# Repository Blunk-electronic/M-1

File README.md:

# SYSTEM M-1
## An OpenSource Boundary Scan Test System (JTAG / IEEE1149.x) for:
- design checking
- low level hardware testing and repairing
- detection of opens, shorts, misloaded parts
- bring-up of prototypes and systems
- system testing in the field

### Test Pattern Generators and UUT data structures open for:
- interaction with In-Circuit and Flying Probe Test
- interaction optical inspection (AOI/AXI)
- customer specific requirements and extensions

### Special Features
- highly scripting capable
- files ASCII based and well suitable for version control with git
- programming language to write test programs
- runs natively on Linux
- source code written in Ada (for mission critical applications)
- rugged boundary scan controller hardware for industrial and educational purposes

### Boundary Scan Controller OpenSource:

- the boundary scan controller for training, development and education:

### Why Ada ??
- The only programming language that provides a robust and strong typing system is Ada.
- Objects and structures within such a test system are very complex things and require sound modelling.
- If saftey/mission critical and military applications use Ada, then is must be good for such a system as well.
- Ada is defined by ISO/IEC 8652:2012 and MIL-STD-1815
- Ada is beautiful :-)

### More Download Stuff
- find training material and user manual at http://www.blunk-electronic.de/products.html

### Collaboration
- We need a nice web site for the project.
- You are highly welcome !

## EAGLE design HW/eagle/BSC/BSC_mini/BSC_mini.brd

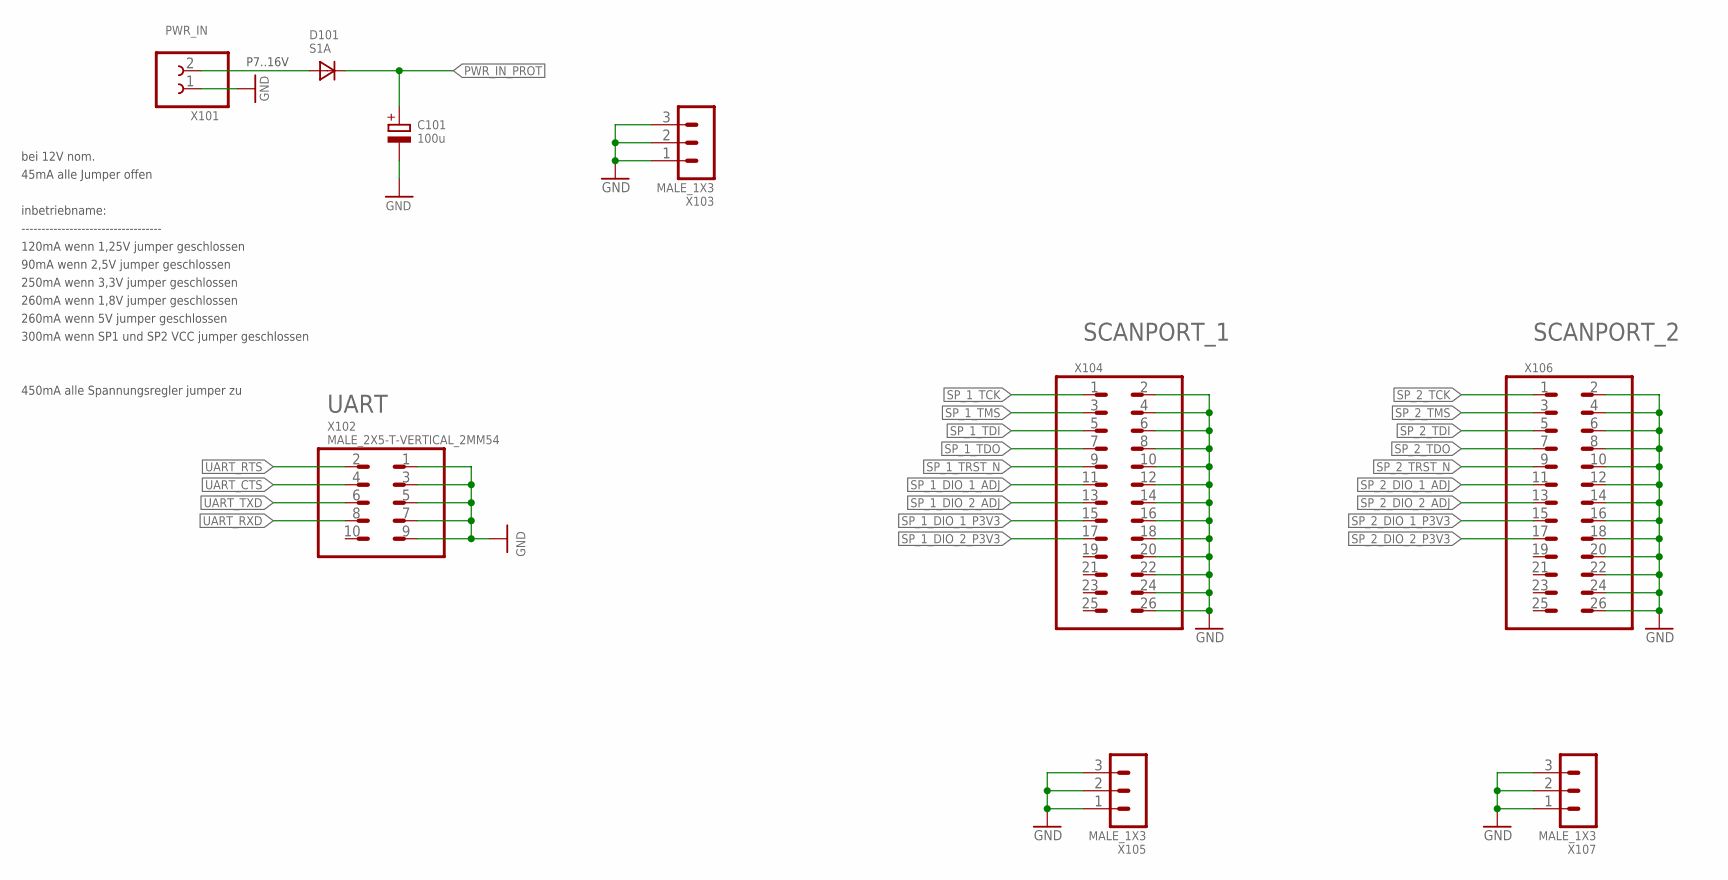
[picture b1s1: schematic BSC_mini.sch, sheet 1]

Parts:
C101: 100u; S_RADIAL_10MM; PART_CODE_BEL C_PAC_S_RADIAL_10mm_VAL_100u_Vmax_50V
D101: S1A; S_DO214AC; PART_CODE_BEL D_PAC_S_DO214AC_VAL_S1A
X101: CLAMP_1X2-T-2.5MM; T_WIRE_CLAMP_1X2_PITCH_2MM5
X102: MALE_2X5-T-VERTICAL_2MM54; T_MALE_2X5_VERTICAL_PITCH_2MM54
X103, X105, X107: MALE_1X3; T_MALE_3X1_VERTICAL
X104, X106: MALE_2X13-T-VERTICAL_PITCH_2MM54; T_MALE_2X13_VERTICAL_PITCH_2MM54

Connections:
GND: C101.-, X101.1, X102.1, X102.3, X102.5, X102.7, X102.9, X103.1, X103.2, X103.3, X104.2, X104.4, X104.6, X104.8, X104.10, X104.12, X104.14, X104.16, X104.18, X104.20, X104.22, X104.24, X104.26, X105.1, X105.2, X105.3, X106.2, X106.4, X106.6, X106.8, X106.10, X106.12, X106.14, X106.16, X106.18, X106.20, X106.22, X106.24, X106.26, X107.1, X107.2, X107.3; also elsewhere on the board
PWR_IN: D101.A, X101.2
PWR_IN_PROT: C101.+, D101.C; also elsewhere on the board
SP_1_DIO_1_ADJ: X104.11; also elsewhere on the board
SP_1_DIO_1_P3V3: X104.15; also elsewhere on the board
SP_1_DIO_2_ADJ: X104.13; also elsewhere on the board
SP_1_DIO_2_P3V3: X104.17; also elsewhere on the board
SP_1_TCK: X104.1; also elsewhere on the board
SP_1_TDI: X104.5; also elsewhere on the board
SP_1_TDO: X104.7; also elsewhere on the board
SP_1_TMS: X104.3; also elsewhere on the board
SP_1_TRST_N: X104.9; also elsewhere on the board
SP_2_DIO_1_ADJ: X106.11; also elsewhere on the board
SP_2_DIO_1_P3V3: X106.15; also elsewhere on the board
SP_2_DIO_2_ADJ: X106.13; also elsewhere on the board
SP_2_DIO_2_P3V3: X106.17; also elsewhere on the board
SP_2_TCK: X106.1; also elsewhere on the board
SP_2_TDI: X106.5; also elsewhere on the board
SP_2_TDO: X106.7; also elsewhere on the board
SP_2_TMS: X106.3; also elsewhere on the board
SP_2_TRST_N: X106.9; also elsewhere on the board
UART_CTS: X102.4; also elsewhere on the board
UART_RTS: X102.2; also elsewhere on the board
UART_RXD: X102.8; also elsewhere on the board
UART_TXD: X102.6; also elsewhere on the board

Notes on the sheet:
P7..16V
bei 12V nom.
45mA alle Jumper offen
450mA alle Spannungsregler jumper zu
120mA wenn 1,25V jumper geschlossen
inbetriebname:
-----------------------------------
90mA wenn 2,5V jumper geschlossen
250mA wenn 3,3V jumper geschlossen
260mA wenn 1,8V jumper geschlossen
260mA wenn 5V jumper geschlossen
300mA wenn SP1 und SP2 VCC jumper geschlossen

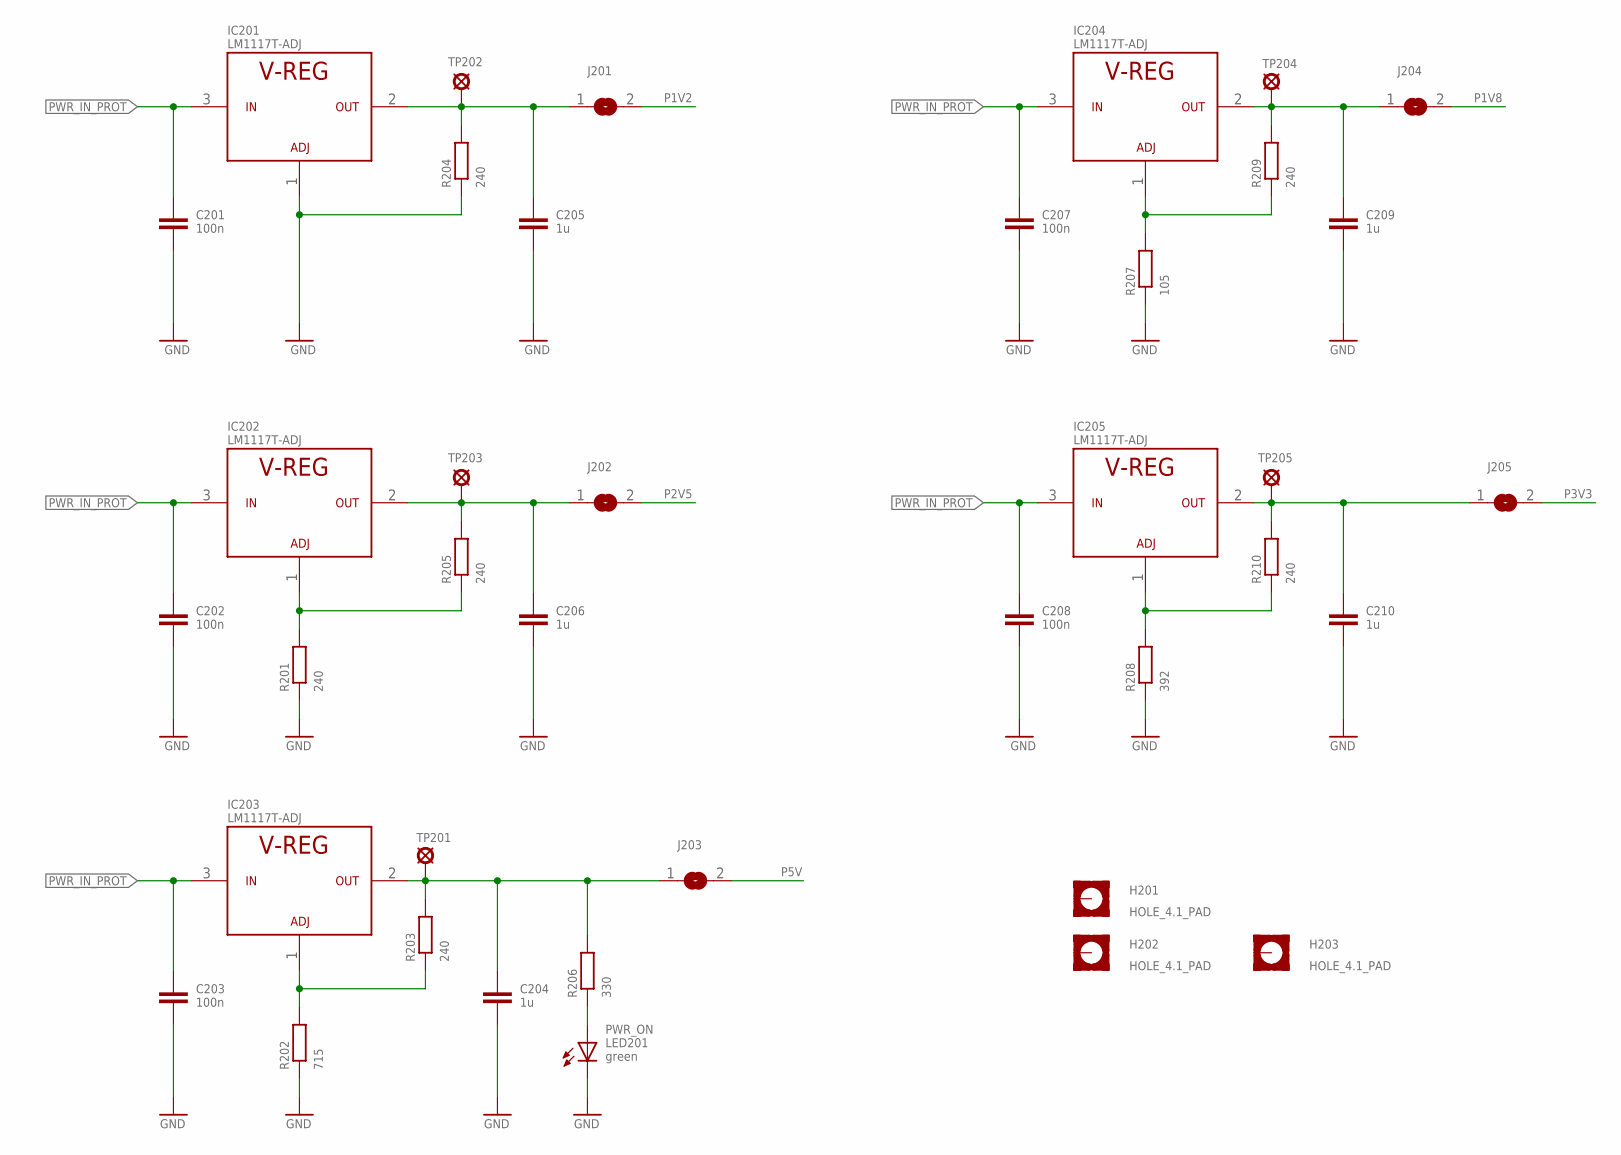
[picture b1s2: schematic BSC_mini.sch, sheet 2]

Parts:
C201, C202, C203, C207, C208: 100n; S_0805; PART_CODE_BEL C_PAC_S_0805_VAL_100n
C204, C205, C206, C209, C210: 1u; S_0805; PART_CODE_BEL C_PAC_S_0805_VAL_1u
H201, H202, H203: HOLE_4.1_PAD; 4.1_PAD
IC201, IC202, IC203, IC204: LM1117T-ADJ; T_TO220-3_VERTICAL; PART_CODE_BEL IC_PAC_T_TO220-3_VERTICAL_VAL_LM1117T-A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
IC205: LM1117T-ADJ; T_TO220-3_HORIZONTAL; PART_CODE_BEL IC_PAC_T_TO220-3_HORIZONTAL_VAL_LM1117T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
J201, J202, J203, J204, J205: SOLDER_JUMPER-N; S_SOLDER_JUMPER_NARROW
LED201: green; S_0805; PART_CODE_BEL LED_PAC_S_0805_VAL_green
R201, R203, R204, R205, R209, R210: 240; S_0805; PART_CODE_BEL R_PAC_S_0805_VAL_240
R202: 715; S_0805; PART_CODE_BEL R_PAC_S_0805_VAL_715
R206: 330; S_0805; PART_CODE_BEL R_PAC_S_0805_VAL_330
R207: 105; S_0805; PART_CODE_BEL R_PAC_S_0805_VAL_105
R208: 392; S_0805; PART_CODE_BEL R_PAC_S_0805_VAL_392
TP201, TP204: TEST_POINT_T_SMALL; T_TEST_POINT_SMALL
TP202: +1V2; T_TEST_POINT_SMALL
TP203, TP205: +2V5; T_TEST_POINT_SMALL

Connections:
GND: C201.2, C202.2, C203.2, C204.2, C205.2, C206.2, C207.2, C208.2, C209.2, C210.2, IC201.1 (AJD), LED201.C, R201.1, R202.1, R204.1, R207.1, R208.1; also elsewhere on the board
P1V2: J201.2; also elsewhere on the board
P1V8: J204.2; also elsewhere on the board
P2V5: J202.2; also elsewhere on the board
P3V3: J205.2; also elsewhere on the board
P5V: J203.2; also elsewhere on the board
PWR_ADJ_P1V8: IC204.1 (AJD), R207.2, R209.1
PWR_ADJ_P2V5: IC202.1 (AJD), R201.2, R205.1
PWR_ADJ_P3V3: IC205.1 (AJD), R208.2, R210.1
PWR_ADJ_P5V: IC203.1 (AJD), R202.2, R203.1
PWR_IN_PROT: C201.1, C202.1, C203.1, C207.1, C208.1, IC201.3 (IN), IC202.3 (IN), IC203.3 (IN), IC204.3 (IN), IC205.3 (IN); also elsewhere on the board
PWR_LED_P5V: LED201.A, R206.1
PWR_P1V2: C205.1, IC201.2 (OUT), J201.1, R204.2, TP202.1
PWR_P1V8: C209.1, IC204.2 (OUT), J204.1, R209.2, TP204.1
PWR_P2V5: C206.1, IC202.2 (OUT), J202.1, R205.2, TP203.1
PWR_P3V3: C210.1, IC205.2 (OUT), J205.1, R210.2, TP205.1
PWR_P5V: C204.1, IC203.2 (OUT), J203.1, R203.2, R206.2, TP201.1

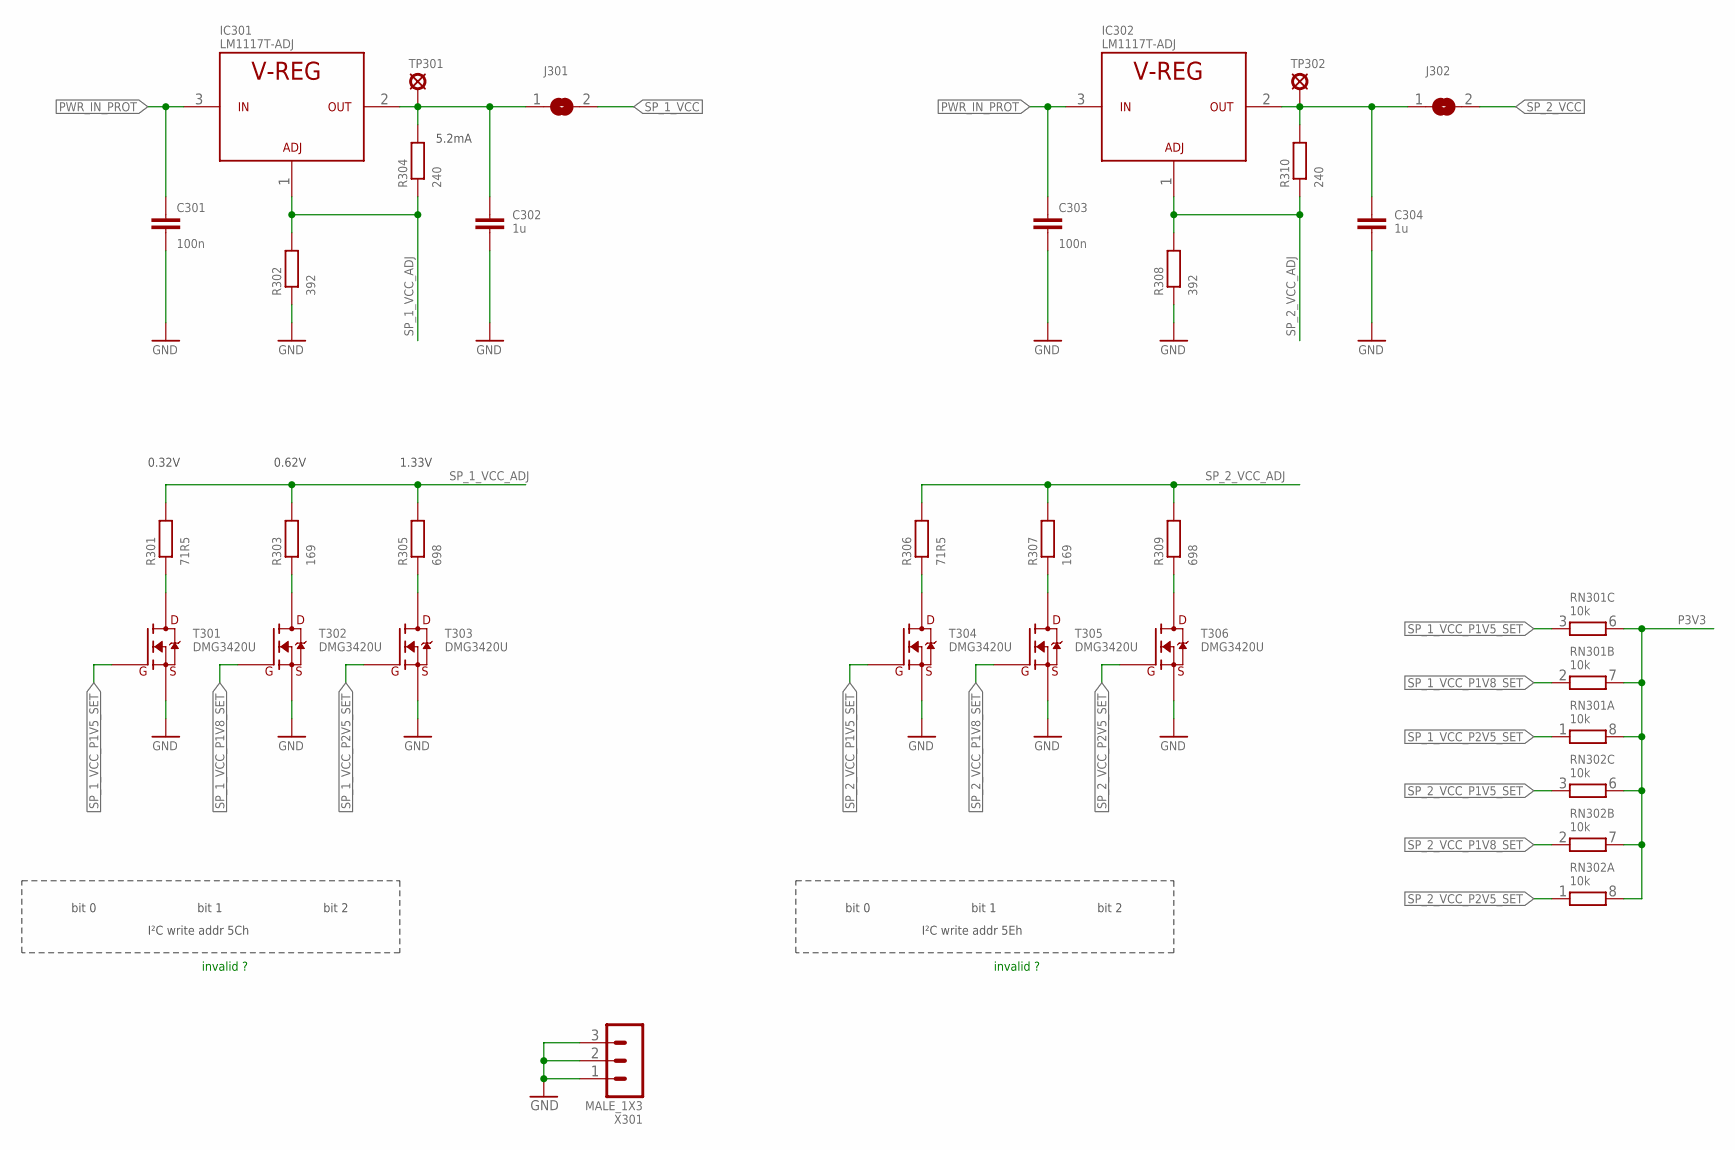
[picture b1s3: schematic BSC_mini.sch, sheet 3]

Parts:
C301, C303: 100n; S_0805; PART_CODE_BEL C_PAC_S_0805_VAL_100n
C302, C304: 1u; S_0805; PART_CODE_BEL C_PAC_S_0805_VAL_1u
IC301, IC302: LM1117T-ADJ; T_TO220-3_VERTICAL; PART_CODE_BEL IC_PAC_T_TO220-3_VERTICAL_VAL_LM1117T-A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
J301, J302: SOLDER_JUMPER-N; S_SOLDER_JUMPER_NARROW
R301, R306: 71R5; S_0805; PART_CODE_BEL R_PAC_S_0805_VAL_71R5
R302, R308: 392; S_0805; PART_CODE_BEL R_PAC_S_0805_VAL_392
R303, R307: 169; S_0805; PART_CODE_BEL R_PAC_S_0805_VAL_169
R304, R310: 240; S_0805; PART_CODE_BEL R_PAC_S_0805_VAL_240
R305, R309: 698; S_0805; PART_CODE_BEL R_PAC_S_0805_VAL_698
RN301, RN302: 10k; S_1206_4X; PART_CODE_BEL RN_PAC_S_1206_4X_VAL_10k
T301, T302, T303, T304, T305, T306: DMG3420U; S_SOT23; PART_CODE_BEL T_PAC_S_SOT23_VAL_DMG3420U
TP301, TP302: TEST_POINT_T_SMALL; T_TEST_POINT_SMALL
X301: MALE_1X3; T_MALE_3X1_VERTICAL

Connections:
GND: C301.2, C302.2, C303.2, C304.2, R302.1, R308.1, T301.2 (S), T302.2 (S), T303.2 (S), T304.2 (S), T305.2 (S), T306.2 (S), X301.1, X301.2, X301.3; also elsewhere on the board
P3V3: RN301.6 (2), RN301.7 (2), RN301.8 (2), RN302.6 (2), RN302.7 (2), RN302.8 (2); also elsewhere on the board
PWR_IN_PROT: C301.1, C303.1, IC301.3 (IN), IC302.3 (IN); also elsewhere on the board
SP_1_VCC: J301.2; also elsewhere on the board
SP_1_VCC_ADJ: IC301.1 (AJD), R301.2, R302.2, R303.2, R304.1, R305.2
SP_1_VCC_P1V5_D: R301.1, T301.3 (D)
SP_1_VCC_P1V5_SET: RN301.3 (1), T301.1 (G); also elsewhere on the board
SP_1_VCC_P1V8_D: R303.1, T302.3 (D)
SP_1_VCC_P1V8_SET: RN301.2 (1), T302.1 (G); also elsewhere on the board
SP_1_VCC_P2V5_D: R305.1, T303.3 (D)
SP_1_VCC_P2V5_SET: RN301.1, T303.1 (G); also elsewhere on the board
SP_1_VCC_REG: C302.1, IC301.2 (OUT), J301.1, R304.2, TP301.1
SP_2_VCC: J302.2; also elsewhere on the board
SP_2_VCC_ADJ: IC302.1 (AJD), R306.2, R307.2, R308.2, R309.2, R310.1
SP_2_VCC_P1V5_D: R306.1, T304.3 (D)
SP_2_VCC_P1V5_SET: RN302.3 (1), T304.1 (G); also elsewhere on the board
SP_2_VCC_P1V8_D: R307.1, T305.3 (D)
SP_2_VCC_P1V8_SET: RN302.2 (1), T305.1 (G); also elsewhere on the board
SP_2_VCC_P2V5_D: R309.1, T306.3 (D)
SP_2_VCC_P2V5_SET: RN302.1, T306.1 (G); also elsewhere on the board
SP_2_VCC_REG: C304.1, IC302.2 (OUT), J302.1, R310.2, TP302.1

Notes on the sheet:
0.32V
0.62V
1.33V
bit 0
bit 1
bit 2
I²C write addr 5Ch
I²C write addr 5Eh
invalid ?
5.2mA

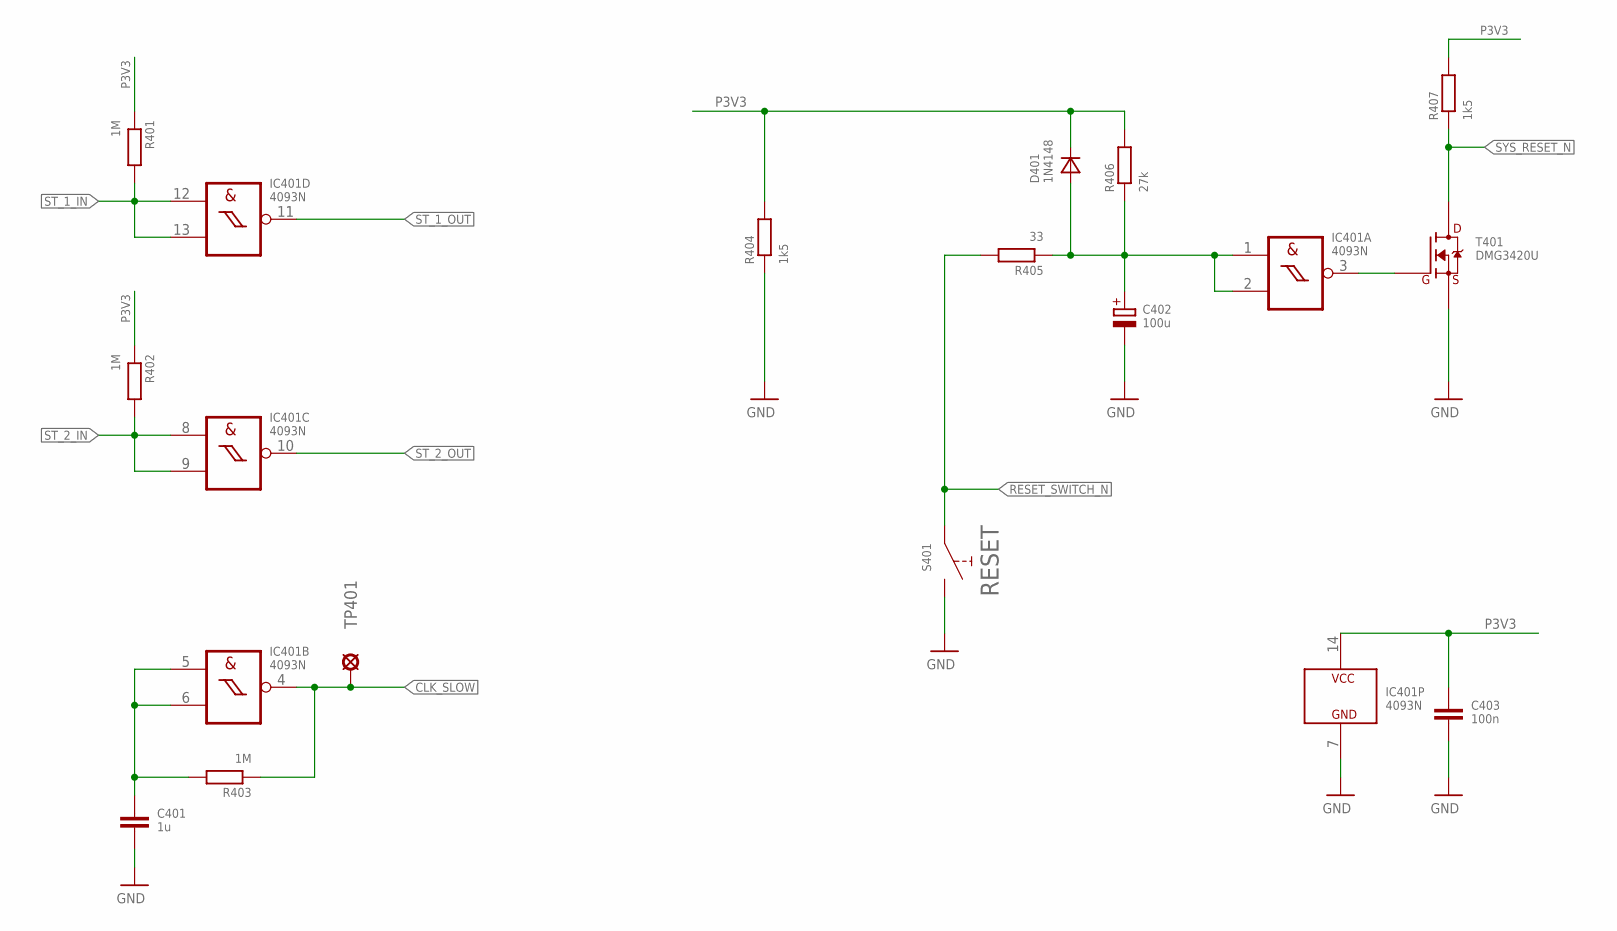
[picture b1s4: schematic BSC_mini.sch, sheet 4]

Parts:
C401: 1u; S_0805; PART_CODE_BEL C_PAC_S_0805_VAL_1u
C402: 100u; S_6032; PART_CODE_BEL C_PAC_S_6032_VAL_100u_Vmax_16V
C403: 100n; S_0805; PART_CODE_BEL C_PAC_S_0805_VAL_100n
D401: 1N4148; S_SOD123
IC401: 4093N; T_NDIP14
R401, R402, R403: 1M; S_0805; PART_CODE_BEL R_PAC_S_0805_VAL_1M
R404, R407: 1k5; S_0805; PART_CODE_BEL R_PAC_S_0805_VAL_1k5
R405: 33; S_0805; PART_CODE_BEL R_PAC_S_0805_VAL_33
R406: 27k; S_0805; PART_CODE_BEL R_PAC_S_0805_VAL_27k
S401: PUSH_BUTTON_T_6X6MM; T_PUSH_BUTTON_6X6; PART_CODE_BEL S_PAC_T_PUSH_BUTTON_6X6mm
T401: DMG3420U; S_SOT23; PART_CODE_BEL T_PAC_S_SOT23_VAL_DMG3420U
TP401: clk_slow; T_TEST_POINT_SMALL

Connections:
CLK_SLOW: IC401.4 (O), R403.1, TP401.1; also elsewhere on the board
GND: C401.2, C402.-, C403.2, IC401.7 (GND), R404.1, S401.2 (B1), S401.4 (B1), T401.2 (S); also elsewhere on the board
OSC_RC: C401.1, IC401.5 (I0), IC401.6 (I1), R403.2
P3V3: C403.1, D401.C, IC401.14 (VCC), R401.1, R402.1, R404.2, R406.2, R407.2; also elsewhere on the board
RESET_RC_N: C402.+, D401.A, IC401.1 (I0), IC401.2 (I1), R405.1, R406.1
RESET_SWITCH_N: R405.2, S401.1 (A1), S401.3 (A1); also elsewhere on the board
ST_1_IN: IC401.12 (I0), IC401.13 (I1), R401.2; also elsewhere on the board
ST_1_OUT: IC401.11 (O); also elsewhere on the board
ST_2_IN: IC401.8 (I0), IC401.9 (I1), R402.2; also elsewhere on the board
ST_2_OUT: IC401.10 (O); also elsewhere on the board
SYS_RESET: IC401.3 (O), T401.1 (G)
SYS_RESET_N: R407.1, T401.3 (D); also elsewhere on the board

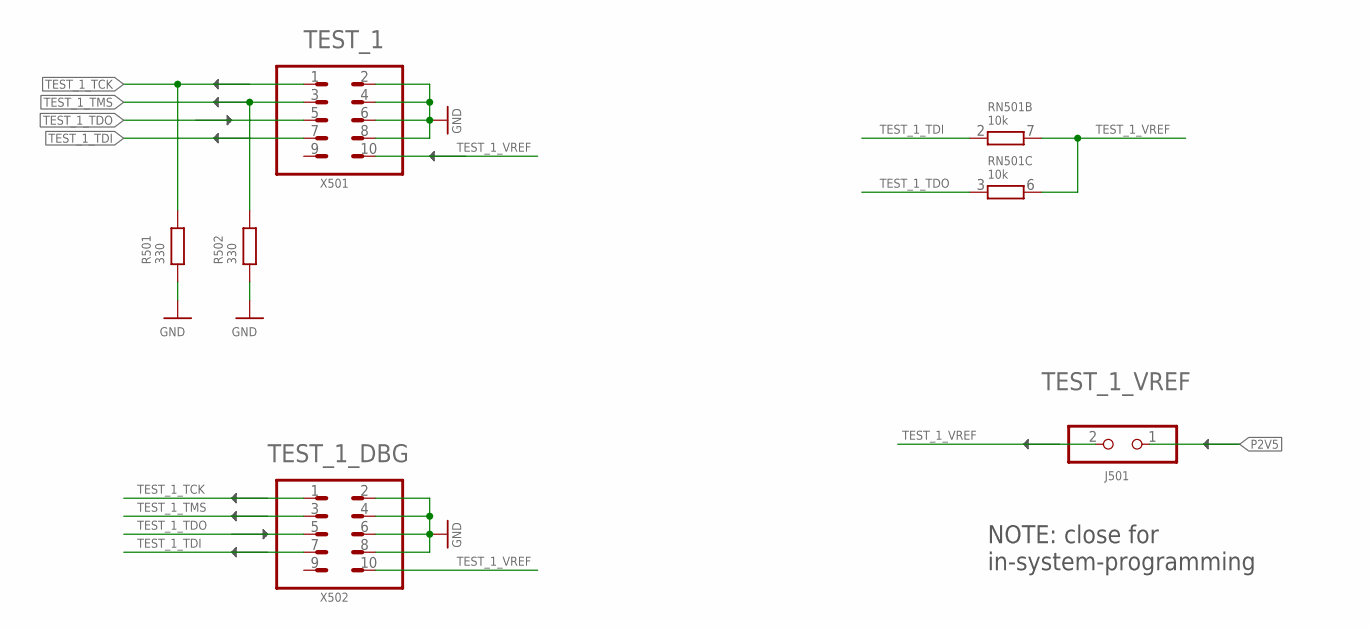
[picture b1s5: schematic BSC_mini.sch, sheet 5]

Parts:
J501: JUMPER_1X2-T-VERTICAL_GRID_2.54MM; T_MALE_2X1_VERTICAL_PITCH_2MM54
R501, R502: 330; S_0805; PART_CODE_BEL R_PAC_S_0805_VAL_330
RN501: 10k; S_1206_4X; PART_CODE_BEL RN_PAC_S_1206_4X_VAL_10k
X501, X502: MALE_2X5-T-VERTICAL_2MM54; T_MALE_2X5_VERTICAL_PITCH_2MM54

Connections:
GND: R501.1, R502.1, X501.2, X501.4, X501.6, X501.8, X502.2, X502.4, X502.6, X502.8; also elsewhere on the board
P2V5: J501.1; also elsewhere on the board
TEST_1_TCK: R501.2, X501.1, X502.1; also elsewhere on the board
TEST_1_TDI: RN501.2 (1), X501.7, X502.7; also elsewhere on the board
TEST_1_TDO: RN501.3 (1), X501.5, X502.5; also elsewhere on the board
TEST_1_TMS: R502.2, X501.3, X502.3; also elsewhere on the board
TEST_1_VREF: J501.2, RN501.6 (2), RN501.7 (2), X501.10, X502.10

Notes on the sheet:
NOTE: close for in-system-programming

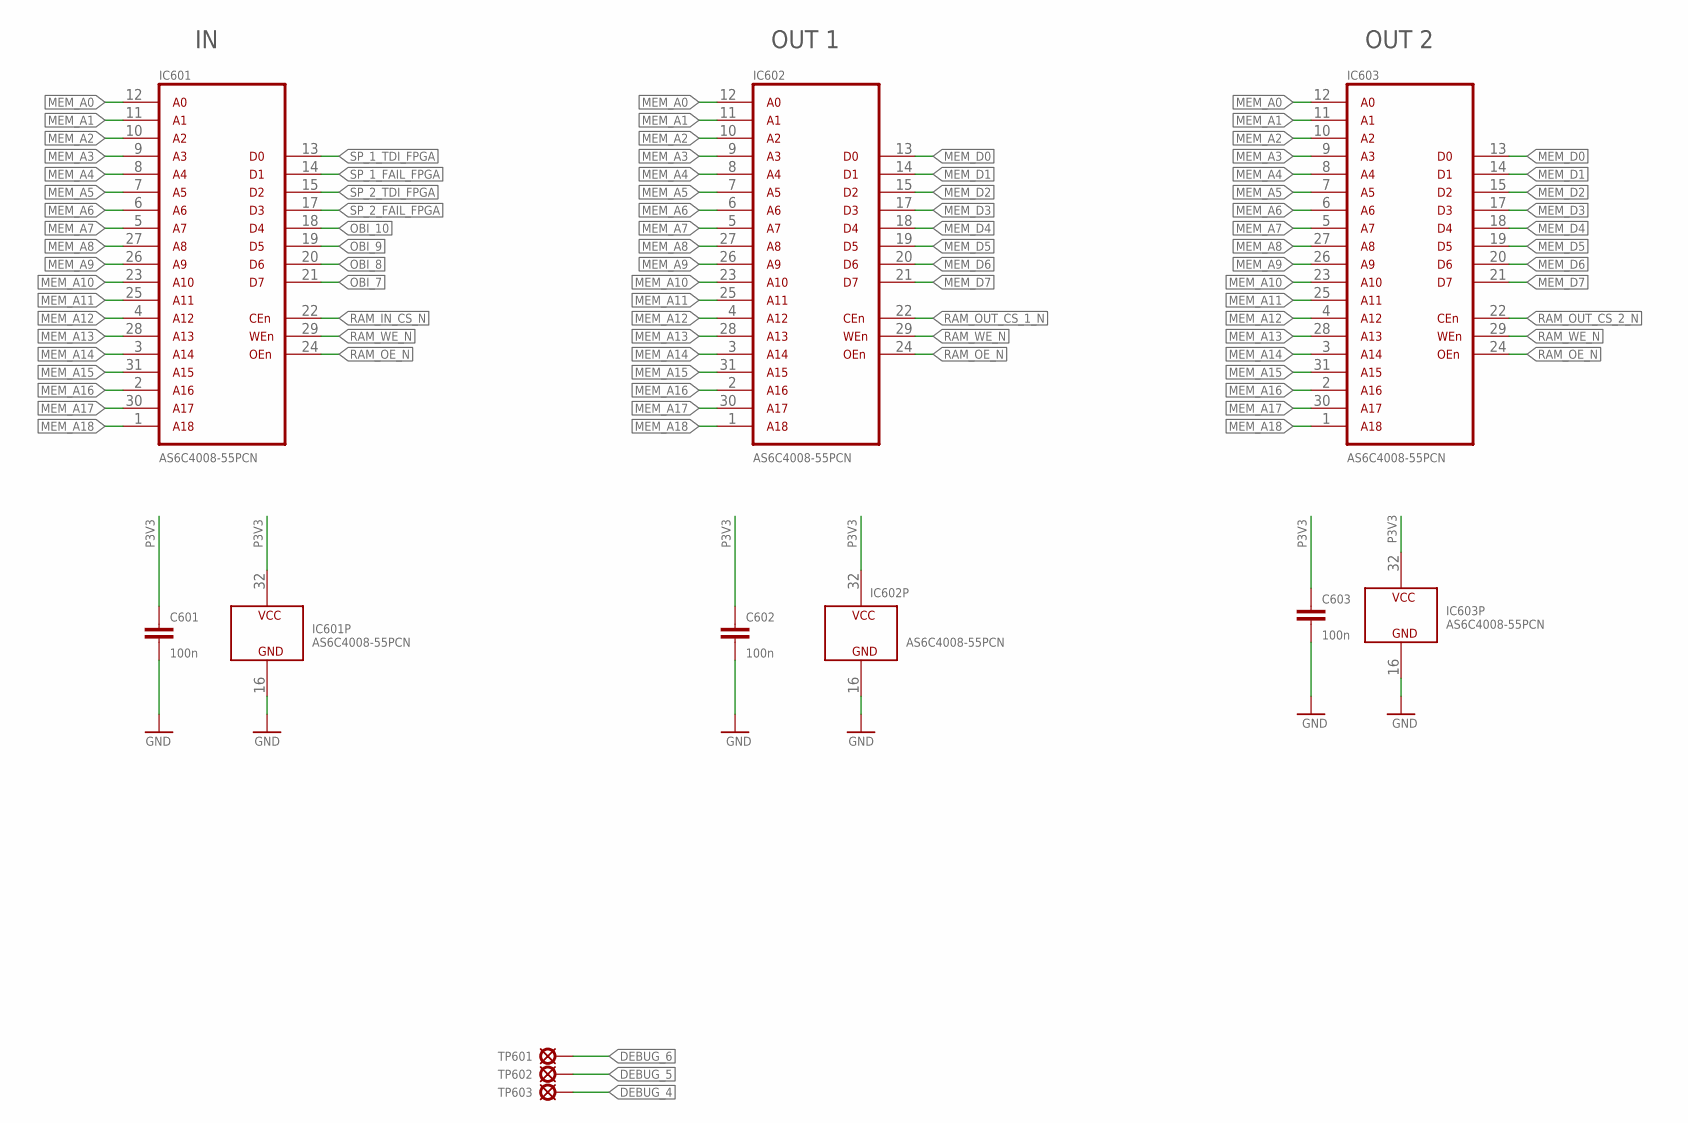
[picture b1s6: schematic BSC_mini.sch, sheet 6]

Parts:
C601, C602, C603: 100n; S_0805; PART_CODE_BEL C_PAC_S_0805_VAL_100n
IC601, IC602, IC603: AS6C4008-55PCN; T_NDIP32; PART_CODE_BEL IC_PAC_T_NDIP32_VAL_AS6C4008-55PCN
TP601, TP602, TP603: TEST_POINT_T_SMALL; T_TEST_POINT_SMALL

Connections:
DEBUG_4: TP603.1; also elsewhere on the board
DEBUG_5: TP602.1; also elsewhere on the board
DEBUG_6: TP601.1; also elsewhere on the board
GND: C601.2, C602.2, C603.2, IC601.16 (GND), IC602.16 (GND), IC603.16 (GND); also elsewhere on the board
MEM_A0: IC601.12 (A0), IC602.12 (A0), IC603.12 (A0); also elsewhere on the board
MEM_A1: IC601.11 (A1), IC602.11 (A1), IC603.11 (A1); also elsewhere on the board
MEM_A2: IC601.10 (A2), IC602.10 (A2), IC603.10 (A2); also elsewhere on the board
MEM_A3: IC601.9 (A3), IC602.9 (A3), IC603.9 (A3); also elsewhere on the board
MEM_A4: IC601.8 (A4), IC602.8 (A4), IC603.8 (A4); also elsewhere on the board
MEM_A5: IC601.7 (A5), IC602.7 (A5), IC603.7 (A5); also elsewhere on the board
MEM_A6: IC601.6 (A6), IC602.6 (A6), IC603.6 (A6); also elsewhere on the board
MEM_A7: IC601.5 (A7), IC602.5 (A7), IC603.5 (A7); also elsewhere on the board
MEM_A8: IC601.27 (A8), IC602.27 (A8), IC603.27 (A8); also elsewhere on the board
MEM_A9: IC601.26 (A9), IC602.26 (A9), IC603.26 (A9); also elsewhere on the board
MEM_A10: IC601.23 (A10), IC602.23 (A10), IC603.23 (A10); also elsewhere on the board
MEM_A11: IC601.25 (A11), IC602.25 (A11), IC603.25 (A11); also elsewhere on the board
MEM_A12: IC601.4 (A12), IC602.4 (A12), IC603.4 (A12); also elsewhere on the board
MEM_A13: IC601.28 (A13), IC602.28 (A13), IC603.28 (A13); also elsewhere on the board
MEM_A14: IC601.3 (A14), IC602.3 (A14), IC603.3 (A14); also elsewhere on the board
MEM_A15: IC601.31 (A15), IC602.31 (A15), IC603.31 (A15); also elsewhere on the board
MEM_A16: IC601.2 (A16), IC602.2 (A16), IC603.2 (A16); also elsewhere on the board
MEM_A17: IC601.30 (A17), IC602.30 (A17), IC603.30 (A17); also elsewhere on the board
MEM_A18: IC601.1 (A18), IC602.1 (A18), IC603.1 (A18); also elsewhere on the board
MEM_D0: IC602.13 (D0), IC603.13 (D0); also elsewhere on the board
MEM_D1: IC602.14 (D1), IC603.14 (D1); also elsewhere on the board
MEM_D2: IC602.15 (D2), IC603.15 (D2); also elsewhere on the board
MEM_D3: IC602.17 (D3), IC603.17 (D3); also elsewhere on the board
MEM_D4: IC602.18 (D4), IC603.18 (D4); also elsewhere on the board
MEM_D5: IC602.19 (D5), IC603.19 (D5); also elsewhere on the board
MEM_D6: IC602.20 (D6), IC603.20 (D6); also elsewhere on the board
MEM_D7: IC602.21 (D7), IC603.21 (D7); also elsewhere on the board
OBI_7: IC601.21 (D7); also elsewhere on the board
OBI_8: IC601.20 (D6); also elsewhere on the board
OBI_9: IC601.19 (D5); also elsewhere on the board
OBI_10: IC601.18 (D4); also elsewhere on the board
P3V3: C601.1, C602.1, C603.1, IC601.32 (VCC), IC602.32 (VCC), IC603.32 (VCC); also elsewhere on the board
RAM_IN_CS_N: IC601.22 (CE); also elsewhere on the board
RAM_OE_N: IC601.24 (OE), IC602.24 (OE), IC603.24 (OE); also elsewhere on the board
RAM_OUT_CS_1_N: IC602.22 (CE); also elsewhere on the board
RAM_OUT_CS_2_N: IC603.22 (CE); also elsewhere on the board
RAM_WE_N: IC601.29 (WE), IC602.29 (WE), IC603.29 (WE); also elsewhere on the board
SP_1_FAIL_FPGA: IC601.14 (D1); also elsewhere on the board
SP_1_TDI_FPGA: IC601.13 (D0); also elsewhere on the board
SP_2_FAIL_FPGA: IC601.17 (D3); also elsewhere on the board
SP_2_TDI_FPGA: IC601.15 (D2); also elsewhere on the board

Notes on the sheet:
OUT 1
OUT 2

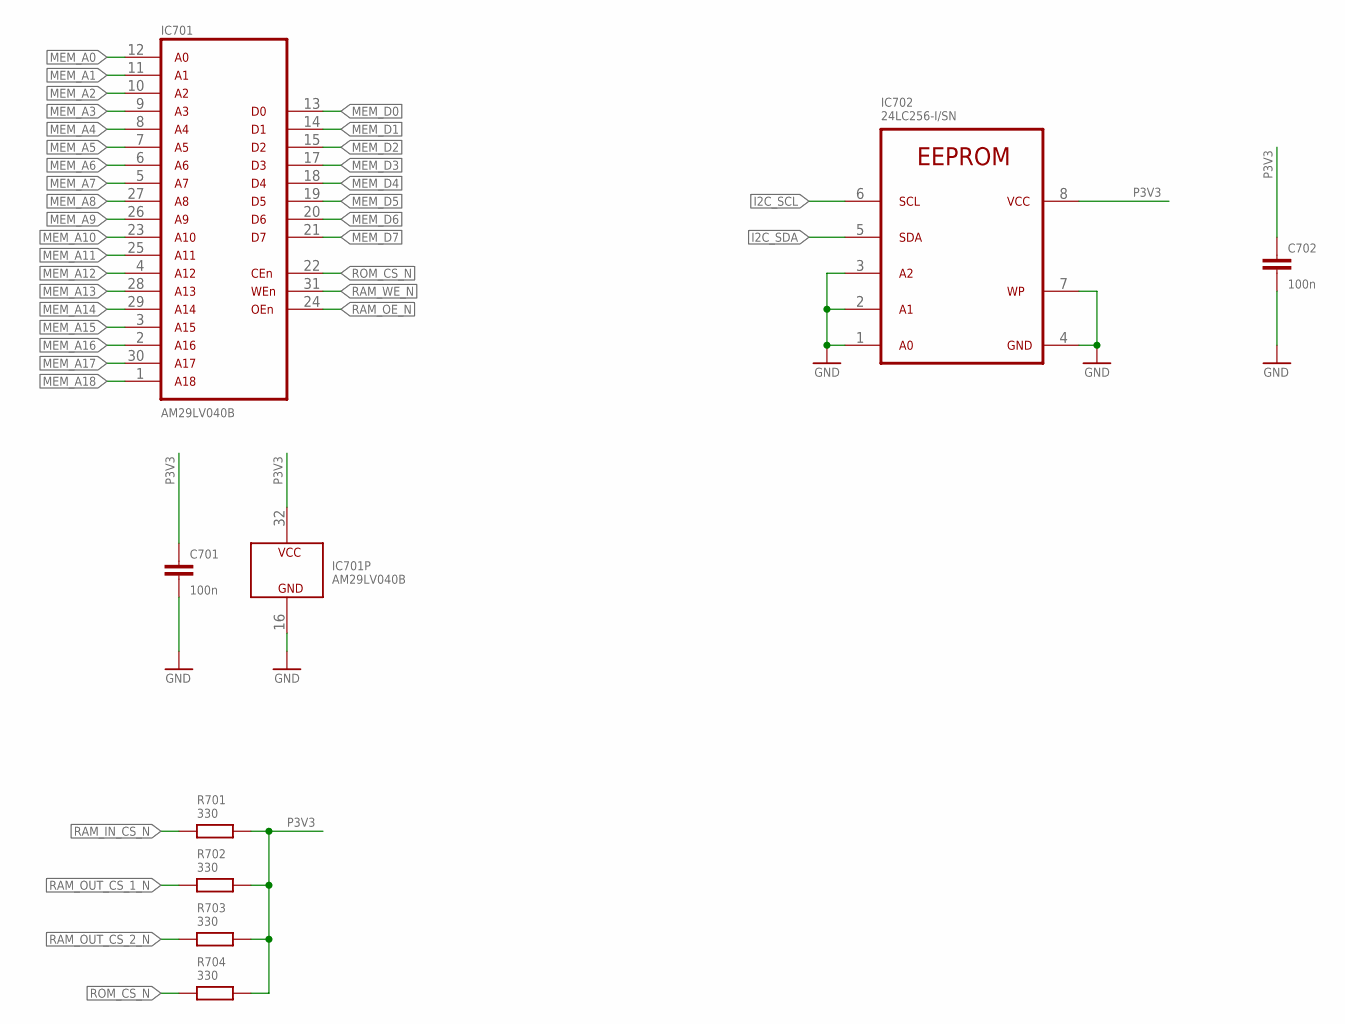
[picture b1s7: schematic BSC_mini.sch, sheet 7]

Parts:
C701, C702: 100n; S_0805; PART_CODE_BEL C_PAC_S_0805_VAL_100n
IC701: AM29LV040B; T_PLCC32; PART_CODE_BEL IC_PAC_T_PLCC32_VAL_AM29LV040B-120JC
IC702: 24LC256-I/SN; S_SOIC8; PART_CODE_BEL IC_PAC_S_SOIC8_VAL_24LC256-I/SN
R701, R702, R703, R704: 330; S_0805; PART_CODE_BEL R_PAC_S_0805_VAL_330

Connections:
GND: C701.2, C702.2, IC701.16 (GND), IC702.1 (A0), IC702.2 (A1), IC702.3 (A2), IC702.4 (GND), IC702.7 (WP); also elsewhere on the board
I2C_SCL: IC702.6 (SCL); also elsewhere on the board
I2C_SDA: IC702.5 (SDA); also elsewhere on the board
MEM_A0: IC701.12 (A0); also elsewhere on the board
MEM_A1: IC701.11 (A1); also elsewhere on the board
MEM_A2: IC701.10 (A2); also elsewhere on the board
MEM_A3: IC701.9 (A3); also elsewhere on the board
MEM_A4: IC701.8 (A4); also elsewhere on the board
MEM_A5: IC701.7 (A5); also elsewhere on the board
MEM_A6: IC701.6 (A6); also elsewhere on the board
MEM_A7: IC701.5 (A7); also elsewhere on the board
MEM_A8: IC701.27 (A8); also elsewhere on the board
MEM_A9: IC701.26 (A9); also elsewhere on the board
MEM_A10: IC701.23 (A10); also elsewhere on the board
MEM_A11: IC701.25 (A11); also elsewhere on the board
MEM_A12: IC701.4 (A12); also elsewhere on the board
MEM_A13: IC701.28 (A13); also elsewhere on the board
MEM_A14: IC701.29 (A14); also elsewhere on the board
MEM_A15: IC701.3 (A15); also elsewhere on the board
MEM_A16: IC701.2 (A16); also elsewhere on the board
MEM_A17: IC701.30 (A17); also elsewhere on the board
MEM_A18: IC701.1 (A18); also elsewhere on the board
MEM_D0: IC701.13 (D0); also elsewhere on the board
MEM_D1: IC701.14 (D1); also elsewhere on the board
MEM_D2: IC701.15 (D2); also elsewhere on the board
MEM_D3: IC701.17 (D3); also elsewhere on the board
MEM_D4: IC701.18 (D4); also elsewhere on the board
MEM_D5: IC701.19 (D5); also elsewhere on the board
MEM_D6: IC701.20 (D6); also elsewhere on the board
MEM_D7: IC701.21 (D7); also elsewhere on the board
P3V3: C701.1, C702.1, IC701.32 (VCC), IC702.8 (VCC), R701.2, R702.2, R703.2, R704.2; also elsewhere on the board
RAM_IN_CS_N: R701.1; also elsewhere on the board
RAM_OE_N: IC701.24 (OE); also elsewhere on the board
RAM_OUT_CS_1_N: R702.1; also elsewhere on the board
RAM_OUT_CS_2_N: R703.1; also elsewhere on the board
RAM_WE_N: IC701.31 (WE); also elsewhere on the board
ROM_CS_N: IC701.22 (CE), R704.1; also elsewhere on the board

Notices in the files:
parts and their libraries:
be_frame: Copyright(C) Blunk electronic
